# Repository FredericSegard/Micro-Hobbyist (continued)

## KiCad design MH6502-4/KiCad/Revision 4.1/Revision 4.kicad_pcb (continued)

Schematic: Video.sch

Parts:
C37, C38: 16pF; C_Disc_D3.4mm_W2.1mm_P2.50mm
C39, C40, C41, C42, C43, C44, C45: 0.1µF; C_Disc_D3.0mm_W1.6mm_P2.50mm
FB1: Ferrite Bead; L_Axial_L5.3mm_D2.2mm_P10.16mm_Horizontal_Vishay_IM-1
J18: INT; PinHeader_1x03_P2.54mm_Vertical
J19: COMPOSITE; RCAJackCUI
Q1: PN2222; TO-92L_Inline_Wide
R2: 470Ω; R_Axial_DIN0207_L6.3mm_D2.5mm_P10.16mm_Horizontal
R3: 75Ω; R_Axial_DIN0207_L6.3mm_D2.5mm_P10.16mm_Horizontal
RV1: 1KΩ; Potentiometer_Bourns_3296W_Vertical
U10: 74HCT04; DIP-14_W7.62mm_Socket
U16: TMS9918A/28A; DIP-40_W15.24mm_Socket
U17, U19, U20: 74HCT574; DIP-20_W7.62mm_Socket
U18: 71256; DIP-28_W7.62mm_Socket
Y2: 10.738635MHz; Crystal_HC18-U_Vertical

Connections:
+5V: C39.1, C40.1, C41.1, C42.1, C43.1, C44.1, FB1.1, U10.14 (VCC), U16.33 (VCC), U17.20 (VCC), U18.28 (VCC), U19.20 (VCC), U20.20 (VCC); also elsewhere on the board
/ACIA/A0: U16.13 (MODE); also elsewhere on the board
/ACIA/D0: U16.17 (D7); also elsewhere on the board
/ACIA/D1: U16.18 (D6); also elsewhere on the board
/ACIA/D2: U16.19 (D5); also elsewhere on the board
/ACIA/D3: U16.20 (D4); also elsewhere on the board
/ACIA/D4: U16.21 (D3); also elsewhere on the board
/ACIA/D5: U16.22 (D2); also elsewhere on the board
/ACIA/D6: U16.23 (D1); also elsewhere on the board
/ACIA/D7: U16.24 (D0); also elsewhere on the board
/Video/AD0: U16.10 (AD0), U17.2 (D0), U19.2 (D0), U20.2 (D0)
/Video/AD1: U16.9 (AD1), U17.3 (D1), U19.3 (D1), U20.3 (D1)
/Video/AD2: U16.8 (AD2), U17.4 (D2), U19.4 (D2), U20.4 (D2)
/Video/AD3: U16.7 (AD3), U17.5 (D3), U19.5 (D3), U20.5 (D3)
/Video/AD4: U16.6 (AD4), U17.6 (D4), U19.6 (D4), U20.6 (D4)
/Video/AD5: U16.5 (AD5), U17.7 (D5), U19.7 (D5), U20.7 (D5)
/Video/AD6: U16.4 (AD6), U17.8 (D6), U19.8 (D6), U20.8 (D6)
/Video/AD7: U16.3 (AD7), U17.9 (D7), U19.9 (D7), U20.9 (D7)
/Video/COL: U10.12, U19.11 (Cp)
/Video/COMP: RV1.2, U16.36 (COMVID)
/Video/FB: C45.1, FB1.2, Q1.3 (C)
/Video/ROW: U10.4, U17.11 (Cp)
/Video/RY: Q1.2 (B), R2.1, RV1.1
/Video/VA0: U17.18 (Q1), U18.10 (A0)
/Video/VA1: U17.17 (Q2), U18.9 (A1)
/Video/VA2: U17.16 (Q3), U18.8 (A2)
/Video/VA3: U17.15 (Q4), U18.7 (A3)
/Video/VA4: U17.14 (Q5), U18.6 (A4)
/Video/VA5: U17.13 (Q6), U18.5 (A5)
/Video/VA6: U17.12 (Q7), U18.4 (A6)
/Video/VA7: U18.3 (A7), U19.18 (Q1)
/Video/VA8: U18.25 (A8), U19.17 (Q2)
/Video/VA9: U18.24 (A9), U19.16 (Q3)
/Video/VA10: U18.21 (A10), U19.15 (Q4)
/Video/VA11: U18.23 (A11), U19.14 (Q5)
/Video/VA12: U18.2 (A12), U19.13 (Q6)
/Video/VA13: U18.26 (A13), U19.12 (Q7)
/Video/VD0: U16.32 (RD0), U18.11 (Q0), U20.19 (Q0)
/Video/VD1: U16.31 (RD1), U18.12 (Q1), U20.18 (Q1)
/Video/VD2: U16.30 (RD2), U18.13 (Q2), U20.17 (Q2)
/Video/VD3: U16.29 (RD3), U18.15 (Q3), U20.16 (Q3)
/Video/VD4: U16.28 (RD4), U18.16 (Q4), U20.15 (Q4)
/Video/VD5: U16.27 (RD5), U18.17 (Q5), U20.14 (Q5)
/Video/VD6: U16.26 (RD6), U18.18 (Q6), U20.13 (Q6)
/Video/VD7: U16.25 (RD7), U18.19 (Q7), U20.12 (Q7)
/Video/VR~W: U10.1, U16.11 (R~W), U18.27 (~WE), U20.1 (OE)
/Video/V~R~W: U10.2, U18.22 (~OE), U20.11 (Cp)
/Video/Y: J19.2, Q1.1 (E), R3.1
/Video/~CAS: U10.9, U16.2 (~CAS), U18.20 (~CS)
/Video/~INT: J18.2, U16.16 (~INT)
/Video/~RAS: U10.3, U16.1 (~RAS)
/~IRQ1: J18.1; also elsewhere on the board
/~NMI: J18.3; also elsewhere on the board
/~RESET: U16.34 (~RESET); also elsewhere on the board
/~VDPCSR: U16.15 (~CSR); also elsewhere on the board
/~VDPCSW: U16.14 (~CSW); also elsewhere on the board
GND: C37.2, C38.2, C39.2, C40.2, C41.2, C42.2, C43.2, C44.2, C45.2, J19.1, R2.2, R3.2, U10.7 (GND), U16.12 (GND), U17.1 (OE), U17.10 (GND), U18.1 (A14), U18.14 (GND), U19.1 (OE), U19.10 (GND), U20.10 (GND); also elsewhere on the board
unnamed: C37.1, U16.39 (XTAL1), Y2.2
unnamed: C38.1, U16.40 (XTAL2), Y2.1
unnamed: U10.10, U10.13
unnamed: U10.8, U10.11

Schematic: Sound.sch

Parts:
C46: 1µF; C_Disc_D3.0mm_W1.6mm_P2.50mm
C47, C48, C49, C50: 0.1µF; C_Disc_D3.0mm_W1.6mm_P2.50mm
J20: MONO; RCAJackCUI
R4, R5, R6, R10: 3K3Ω; R_Axial_DIN0207_L6.3mm_D2.5mm_P10.16mm_Horizontal
R7, R8, R9, R11: 1KΩ; R_Axial_DIN0207_L6.3mm_D2.5mm_P10.16mm_Horizontal
U21, U22, U23, U24: AY-3-8910; DIP-40_W15.24mm_Socket

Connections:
+5V: C47.1, C48.1, C49.1, C50.1, U21.25 (A8), U21.28 (BC2), U21.40 (VCC), U22.25 (A8), U22.28 (BC2), U22.40 (VCC), U23.25 (A8), U23.28 (BC2), U23.40 (VCC), U24.25 (A8), U24.28 (BC2), U24.40 (VCC); also elsewhere on the board
/ACIA/D0: U21.37 (DA0), U22.37 (DA0), U23.37 (DA0), U24.37 (DA0); also elsewhere on the board
/ACIA/D1: U21.36 (DA1), U22.36 (DA1), U23.36 (DA1), U24.36 (DA1); also elsewhere on the board
/ACIA/D2: U21.35 (DA2), U22.35 (DA2), U23.35 (DA2), U24.35 (DA2); also elsewhere on the board
/ACIA/D3: U21.34 (DA3), U22.34 (DA3), U23.34 (DA3), U24.34 (DA3); also elsewhere on the board
/ACIA/D4: U21.33 (DA4), U22.33 (DA4), U23.33 (DA4), U24.33 (DA4); also elsewhere on the board
/ACIA/D5: U21.32 (DA5), U22.32 (DA5), U23.32 (DA5), U24.32 (DA5); also elsewhere on the board
/ACIA/D6: U21.31 (DA6), U22.31 (DA6), U23.31 (DA6), U24.31 (DA6); also elsewhere on the board
/ACIA/D7: U21.30 (DA7), U22.30 (DA7), U23.30 (DA7), U24.30 (DA7); also elsewhere on the board
/BC1: U21.29 (BC1); also elsewhere on the board
/BC2: U22.29 (BC1); also elsewhere on the board
/BC3: U23.29 (BC1); also elsewhere on the board
/BC4: U24.29 (BC1); also elsewhere on the board
/BDIR1: U21.27 (BDIR); also elsewhere on the board
/BDIR2: U22.27 (BDIR); also elsewhere on the board
/BDIR3: U23.27 (BDIR); also elsewhere on the board
/BDIR4: U24.27 (BDIR); also elsewhere on the board
/PSG_CLK: U21.22 (CLK), U22.22 (CLK), U23.22 (CLK), U24.22 (CLK); also elsewhere on the board
/Sound/MONO: C46.2, R4.2, R5.2, R6.2, R10.2
/~RESET: U21.23 (~RESET), U22.23 (~RESET), U23.23 (~RESET), U24.23 (~RESET); also elsewhere on the board
GND: C47.2, C48.2, C49.2, C50.2, J20.1, R7.1, R8.1, R9.1, R11.1, U21.1 (GND), U21.24 (~A9), U22.1 (GND), U22.24 (~A9), U23.1 (GND), U23.24 (~A9), U24.1 (GND), U24.24 (~A9); also elsewhere on the board
unnamed: C46.1, J20.2
unnamed: R4.1, R7.2, U21.3 (CH_B), U21.4 (CH_A), U21.38 (CH_C)
unnamed: R5.1, R8.2, U22.3 (CH_B), U22.4 (CH_A), U22.38 (CH_C)
unnamed: R6.1, R9.2, U23.3 (CH_B), U23.4 (CH_A), U23.38 (CH_C)
unnamed: R10.1, R11.2, U24.3 (CH_B), U24.4 (CH_A), U24.38 (CH_C)

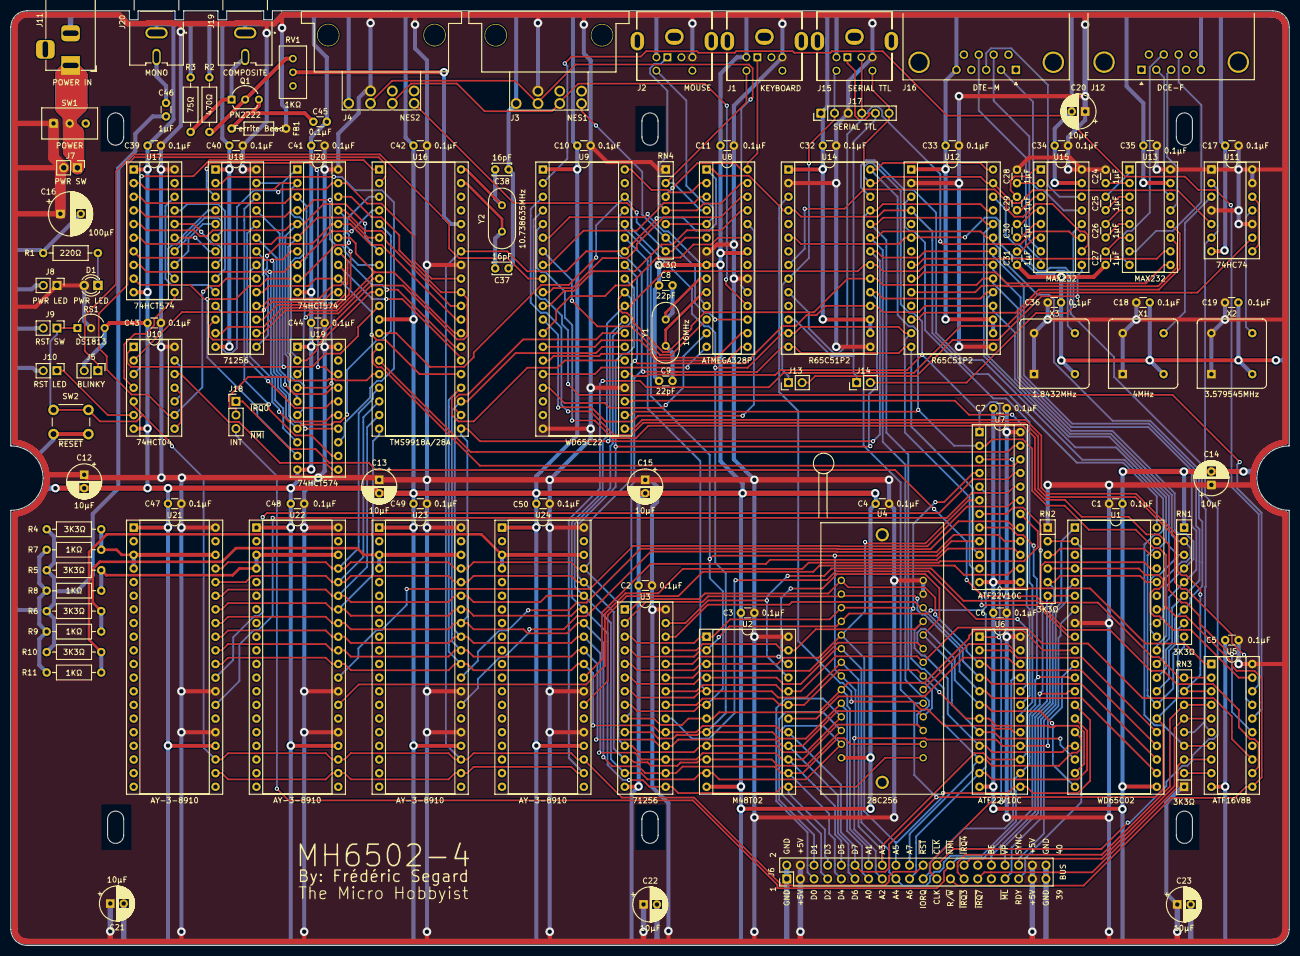
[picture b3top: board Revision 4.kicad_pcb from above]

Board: 2 copper layers, 238.0 x 174.0 mm, 121 parts (0 on the bottom side), 181 nets.

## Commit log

2022-06-03 Added schematic pdf
2022-06-04 Added HM6502-5 backplane (removed termination)
